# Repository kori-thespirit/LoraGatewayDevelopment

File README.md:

# ESP32-S3 Pin Mapping Documentation

Tài liệu này mô tả sơ đồ kết nối chân giữa ESP32-S3 và các module sử dụng trong hệ thống.

---

# 1. Strapping Pins (Boot Configuration)

Các chân này được đọc khi ESP32 khởi động, ảnh hưởng đến chế độ boot và cấu hình phần cứng.

| ESP32-S3 | FUNCTION |
|:---------|:---------|
| GPIO0    | Boot mode select |
| GPIO3    | JTAG source select |
| GPIO45   | Flash voltage select |
| GPIO46   | Boot mode / ROM log control |

---

# 2. LoRa Module (SPI)

Ví dụ module: SX1278 / Ra-02

| ESP32-S3 | LORA |
|:---------|:-----|
| GPIO40   | MISO |
| GPIO39   | SCK |
| GPIO41   | MOSI |
| GPIO42   | NSS (CS) |
| GPIO38   | RST |
| GPIO37   | DIO0 |

---

# 3. RS485 Module (UART)

Ví dụ module: MAX3485 / SP3485

| ESP32-S3 | RS485 |
|:---------|:------|
| GPIO17   | TX |
| GPIO18   | RX |
| GPIO16   | DE |
| GPIO15   | RE |

---

# 4. I2C Devices

Ví dụ: Sensor, LCD, EEPROM

| ESP32-S3 | I2C |
|:---------|:----|
| GPIO8    | SDA |
| GPIO9    | SCL |

---

# 5. SPI Devices (General)

| ESP32-S3 | SPI DEVICE |
|:---------|:-----------|
| GPIO12   | MISO |
| GPIO13   | MOSI |
| GPIO14   | SCK |
| GPIO10   | CS |

---

# 6. UART Debug / Programming

| ESP32-S3 | UART |
|:---------|:-----|
| GPIO43   | TXD0 |
| GPIO44   | RXD0 |

---

# 7. Control Signals

| ESP32-S3 | CONTROL |
|:---------|:--------|
| EN       | Chip enable / Reset |
| 3V3      | Power supply |
| GND      | Ground |

---

# 8. Important Notes

## Strapping Pins Warning

Không nên kéo các chân sau xuống mức LOW khi khởi động:

- GPIO0
- GPIO3
- GPIO45
- GPIO46

Sai cấu hình có thể gây:

- Không boot
- Không nạp code
- Treo hệ thống

## Recommended Pull-up / Pull-down

- GPIO0 → Pull-up 10kΩ
- EN → Pull-up 10kΩ

---

# 9. Project Information

## MCU

ESP32-S3

## Communication

- SPI
- UART
- RS485
- I2C

---

# End of Document

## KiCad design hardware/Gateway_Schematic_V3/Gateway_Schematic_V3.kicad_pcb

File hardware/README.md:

# ESP32-S3 Pin
| Pin Number | Pin Name | Function | Device |
| :--- | :--- | :--- | :--- |
| 5 | GPIO5 (ESP_TX) | HMI_RX | HMI Dwin |
| 6 | GPIO6 (ESP_RX) | HMI_TX | HMI Dwin |
| 39 | GPIO1 | LoRA_INTERRUPT | LoRA Module |
| 31 | GPIO38 | RESET | LoRA Module |
| 32 | GPIO39 | SCK | LoRA Module |
| 33 | GPIO40 | MISO | LoRA Module |
| 34 | GPIO41 | MOSI | LoRA Module |
| 35 | GPIO42 | CS | LoRA Module |
| 18 | GPIO10 | I2C_SCL | Module RTC_DS3231 |
| 19 | GPIO11 | I2C_SDA | Module RTC_DS3231 |
| 15 | GPIO3 | SIM_PWRKEY | SIMCOM |
| 7 | GPIO7 | SIM_RESET | SIMCOM |
| 23 | GPIO21 (ESP_TX) | SIM_RX | SIMCOM |
| 24 | GPIO47 (ESP_RX) | SIM_TX | SIMCOM |
| 12 | GPIO8 | CS | W5500_ETHERNET |
| 17 | GPIO9 | INTERRUPT | W5500_ETHERNET |
| 9 | GPIO16 | MOSI | W5500_ETHERNET |
| 10 | GPIO17 | MISO | W5500_ETHERNET |
| 11 | GPIO18 | SPI_CLK | W5500_ETHERNET |
| 22 | GPIO14 | SDIO_CLK | SD CARD |
| 8 | GPIO15 | SDIO_CMD | SD CARD |
| 20 | GPIO12 | SDIO_DATA0 | SD CARD |
| 21 | GPIO13 | SDIO_DATA1 | SD CARD |
| 4 | GPIO4 | SDIO_DATA2 | SD CARD |
| 38 | GPIO2 | SDIO_DATA3 | SD CARD |
| 26 | GPIO45 | SDIO_DET | SD CARD |

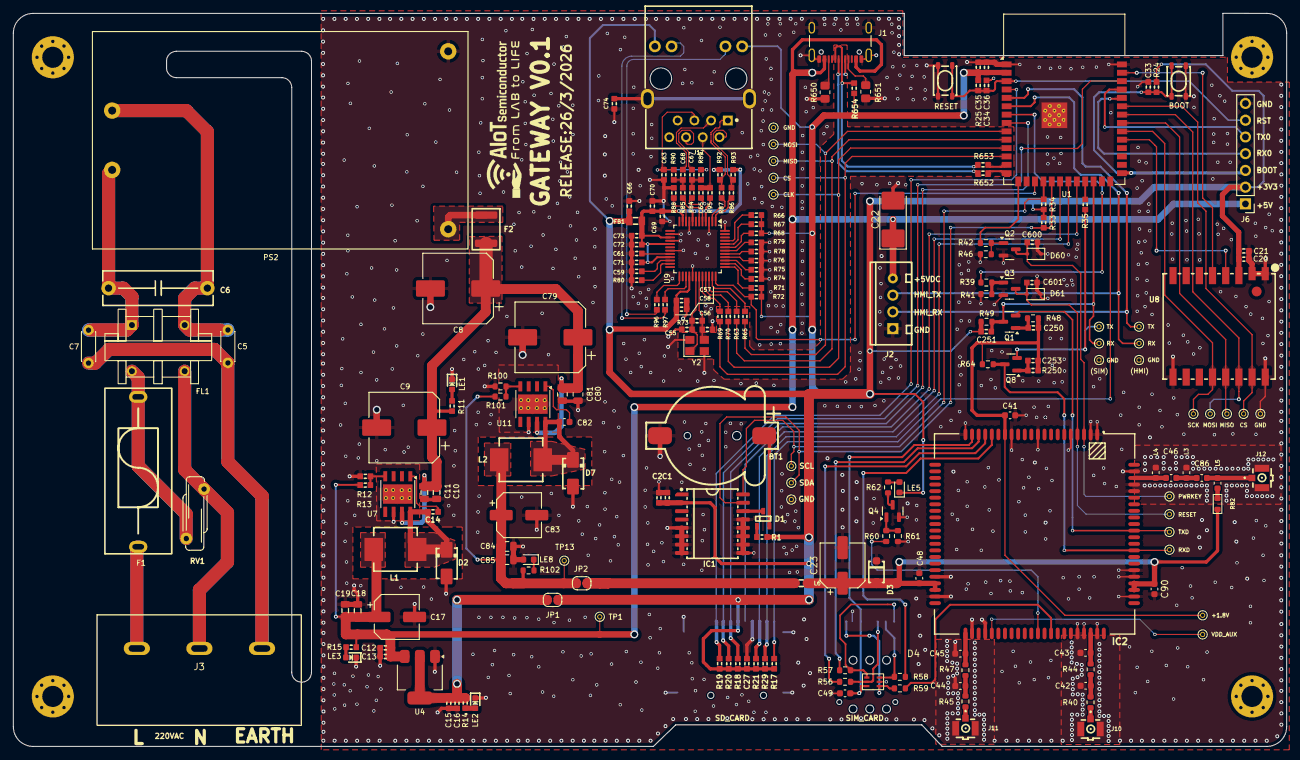
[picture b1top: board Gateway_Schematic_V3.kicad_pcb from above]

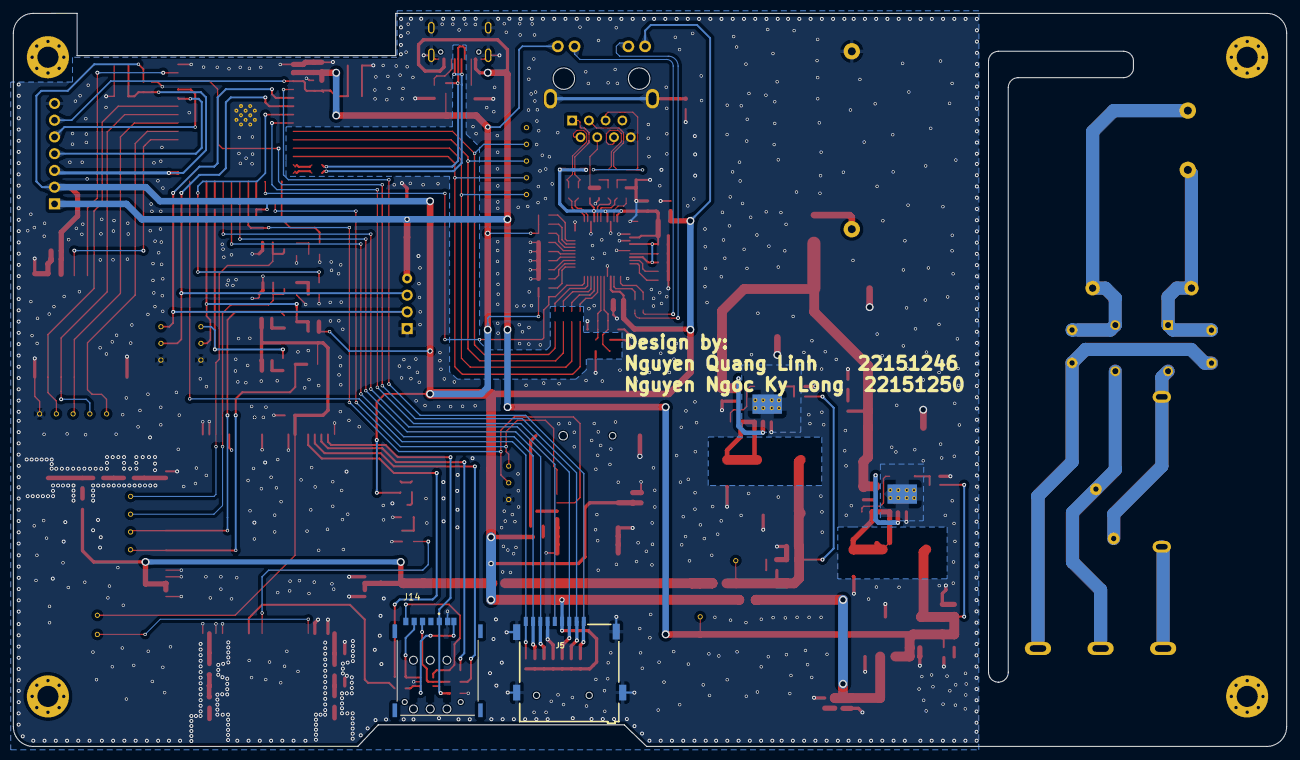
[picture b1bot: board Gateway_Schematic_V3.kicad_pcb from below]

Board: 2 copper layers, 193.2 x 111.3 mm, 222 parts (2 on the bottom side), 132 nets.

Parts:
+1.8V: TestPoint_throughtHole_D1.0mm
BT1: CR1220; BatteryHolder_CR1220
C1, C20, C36, C66: 10uF; C_0603
C2, C13, C16, C21, C27, C33, C35, C58, C69, C70, C71, C72, C73, C600, C601: 100nF; C_0603
C5, C7: 471/2k; C_Disc_D4.3mm_W1.9mm_P5.00mm
C6: 0.1uF/275VAC; C_Rect_L16.5mm_W5.0mm_P15.00mm_MKT
C8, C9, C79: 470uF/35V; CP_Elec_10x10.5
C10, C18: 10uF; C_0805
C11, C19: 100nF; C_0805
C12, C15, C34, C57: 1uF; C_0603
C14, C59, C63: 10nF; C_0603
C17, C83: 330uF/6v3; CP_Elec_6.3x7.7
C22: 100uF/35V/7343; CP_EIA-7132-28_AVX-C_Pad2.72x3.50mm_HandSolder
C23: C_Polarized; CP_Elec_6.3x7.7
C41, C49: 100nF; C_0603_1608Metric
C42, C43, C44, C45: NC; C_0603_1608Metric
C46, C48, C86: 33pF; C_0603_1608Metric
C55, C56: 18pF; C_0603
C61: 4.7uF; C_0603
C65: 22nF; C_0603
C67, C68: 6.8nF; C_0603
C74: 4.7nF; C_0603
C80, C84: 10uF; C_0805_2012Metric
C81, C85: 100nF; C_0805_2012Metric
C82: 10nF; C_0603_1608Metric
C90: 18pF; C_0603_1608Metric
C250, C253: 1nF; C_0603
C251: 470pF; C_0603
CLK: TestPoint_throughtHole_D1.0mm
CS: TestPoint; TestPoint_throughtHole_D1.0mm
CS#2: TestPoint_throughtHole_D1.0mm
D1: BAT54C; SOT23-3
D2, D7: SS54; D_SMA
D3: 5V1; D_SOD-123
D4: SMF05C; SC70-6
D60, D61: PSD12C; D_SOD-323
F1: 2A; Fuse_HolderGlass5x20mm
F2: 1.5A; Fuse_1812_4532Metric
FB1: FerriteBead_Small; L_0805
FL1: 20mH; ACFilterChokeUU9.8
GND: TestPoint; TestPoint_throughtHole_D1.0mm
GND#2, GND#3, GND#4, GND#5: TestPoint; TestPoint_throughtHole_D1.0mm
H1, H1#2, H1#3, H1#4: MountingHole; MountingHole_3.2mm_M3_Pad_Via
IC1: RTC_DS3231M; SOIC-16W_7.5x10.3mm_P1.27mm
IC2: SIM7600CE-H; SIM7600
J1: USB_C_Receptacle_USB2.0_14P; USB_C_Receptacle_GCT_USB4105-xx-A_16P_TopMnt_Horizontal
J2: Conn_01x04_Pin; Conn_XH-P2.54mm-4P
J3: Screw_Terminal_01x03; TerminalBlock_Screw_HB9500_3pin_P9.5mm
J5: MiSD-PP-9P-V1; MicroSD_Socket_9P
J6: Conn_01x07_Pin; PinHeader_1x07_P2.54mm_Vertical
J10, J11, J12: ANT_LTE; Conn_IPEX_ANT
J14: SIM7100-6pin-socket-smd; CUI_NSIM-1-A
J17: HR911105A; HANRUN_RJ45LED_HR911105A
JP1, JP2: SolderJumper_2_Open; SolderJumper-2_P1.3mm_Open_RoundedPad1.0x1.5mm
L1, L2: 15uH; L_6.6x6.6
L3, L4, L5: L; L_0603_1608Metric
L6: L_Ferrite_Small; L_0805
LE1, LE2, LE3: Led; LED_0603
LE5, LE8: Led; LED_0603_1608Metric
MISO: TestPoint; TestPoint_throughtHole_D1.0mm
MISO#2: TestPoint_throughtHole_D1.0mm
MOSI: TestPoint; TestPoint_throughtHole_D1.0mm
MOSI#2: TestPoint_throughtHole_D1.0mm
PS2: HLK-20M12; ACDC_HLK-20MXX
PWRKEY: TestPoint_throughtHole_D1.0mm
Q1, Q8: MMBT3904; SOT-23
Q2, Q3, Q4: BC817; SOT-23
R1: 1K/0603/5%; R_0603
R11, R13: 10k; R_0603
R12: 3k3; R_0603
R14, R15: 1k; R_0603
R17, R18, R19, R20, R21, R24, R25, R29, R33, R34: 10K/0603/1%; R_0603
R35: 100R; R_0603
R39, R42, R48, R49, R60, R64, R100: 4K7; R_0603_1608Metric
R40, R44, R45, R47, R59: 0; R_0603_1608Metric
R41, R46, R61: 47K; R_0603_1608Metric
R56, R57, R58: 22; R_0603_1608Metric
R62: 1K; R_0603_1608Metric
R63, R65, R69, R70, R84, R85, R86, R87: 33R; R_0603
R66, R67, R68, R71, R72, R74, R75, R76, R78, R79, R80: 10K; R_0603
R73: 1M; R_0603
R82: 10 Ohm; R_0603_1608Metric
R88: 12K4/1%; R_0603
R89, R90: 82R; R_0603
R92, R93: 49R9; R_0603
R95: 10R; R_0603
R96, R97: 330; R_0603
R101: 10k; R_0603_1608Metric
R102: 1k; R_0603_1608Metric
R250: 4K7; R_0603
R650, R651: 5K1; R_0805_2012Metric_Pad1.20x1.40mm_HandSolder
R652, R653: 22R; R_0603
R654: 1K5; R_0603
RESET: TestPoint_throughtHole_D1.0mm
RV1: 10D561; RV_Disc_D12mm_W5.8mm_P7.5mm
RX: TestPoint_throughtHole_D1.0mm
RX#2: TestPoint; TestPoint_throughtHole_D1.0mm
RXD: TestPoint_throughtHole_D1.0mm
SCK: TestPoint; TestPoint_throughtHole_D1.0mm
SCL: TestPoint; TestPoint_throughtHole_D1.0mm
SDA: TestPoint; TestPoint_throughtHole_D1.0mm
SW1, SW2: SW_Push; SW_SPST_PTS810
TP1: 5V; TestPoint_throughtHole_D1.0mm
TP13: 4V; TestPoint_throughtHole_D1.0mm
TX: TestPoint_throughtHole_D1.0mm
TX#2: TestPoint; TestPoint_throughtHole_D1.0mm
TXD: TestPoint_throughtHole_D1.0mm
U1: ESP32-S3-WROOM-1
U4: AMS1117-3.3; SOT-223-3_TabPin2
U7, U11: TPS5430DDA; TI_SO-PowerPAD-8_ThermalVias
U8: SX1278 Lora Ra-02; MODULE_RA-02_LORA
U9: W5500; LQFP-48_7x7mm_P0.5mm
VDD_AUX: TestPoint_throughtHole_D1.0mm
Y2: 25MHz; Crystal_SMD_3225-4Pin_3.2x2.5mm

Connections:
+3.3V: C1.2, C2.2, C15.2, C16.2, C20.1, C21.1, C27.2, C35.1, C36.1, C57.1, C58.1, C66.1, C251.1, FB1.2, IC1.2 (VCC), J5.4 (VDD), J6.2, J17.9, J17.12, JP1.1 (A), JP1.2 (B), LE5.1, R1.1, R14.1, R17.1, R18.1, R19.1, R20.1, R21.1, R24.1, R25.1, R29.1, R33.1, R34.1, R49.2, R66.1, R67.1, R68.1, R71.1, R72.1, R654.2, U1.2 (3V3), U4.2 (VO), U8.3 (VDD), U9.28 (VDD)
+4V: C23.1, C48.1, C83.1, C84.1, C85.1, C90.1, D3.1 (K), IC2.38 (VBAT), IC2.39 (VBAT), IC2.62 (VBAT), IC2.63 (VBAT), JP2.1 (A), JP2.2 (B), L2.2, L6.1, L6.2, R82.1, R101.2, R102.1, TP13.1
+5V: C12.2, C13.2, C17.1, C18.1, C19.1, C22.1, J1.A4 (VBUS), J1.A9 (VBUS), J1.B4 (VBUS), J1.B9 (VBUS), J2.4, J6.1, L1.2, R13.2, R15.1, TP1.1, U4.3 (VI)
+12V: C8.1, C9.1, C10.1, C11.1, C79.1, C80.1, C81.1, F2.2, R11.1, U7.7 (VIN), U11.7 (VIN)
/ESP32-S3/BOOT: C33.1, J6.3, R24.2, SW1.2, U1.27 (IO0)
/ESP32-S3/ESP.CLK: J5.5 (CLK), U1.22 (IO14)
/ESP32-S3/ESP.CMD: J5.3 (CMD), R18.2, U1.8 (IO15)
/ESP32-S3/ESP.DATA0: J5.7 (DAT0), R21.2, U1.20 (IO12)
/ESP32-S3/ESP.DATA1: J5.8 (DAT1), R29.2, U1.21 (IO13)
/ESP32-S3/ESP.DATA2: J5.1 (DAT2), R19.2, U1.4 (IO4)
/ESP32-S3/ESP.DATA3: J5.2 (DAT3/CD), R20.2, U1.38 (IO2)
/ESP32-S3/ESP.DET: J5.9 (DET), R17.2, U1.26 (IO45)
/ESP32-S3/ESP.SCL: IC1.16 (SCL), R34.2, SCL.1, U1.18 (IO10)
/ESP32-S3/ESP.SDA: IC1.15 (SDA), R33.2, SDA.1, U1.19 (IO11)
/ESP32-S3/ESP.USB_N: R653.2, U1.13 (IO19)
/ESP32-S3/ESP.USB_P: R652.2, U1.14 (IO20)
/ESP32-S3/ESP_ETH.CLK: CLK.1, R70.1, U1.11 (IO18)
/ESP32-S3/ESP_ETH.MISO: MISO#2.1, R63.1, U1.10 (IO17)
/ESP32-S3/ESP_ETH.MOSI: MOSI#2.1, R65.1, U1.9 (IO16)
/ESP32-S3/ESP_ETH_CS: CS#2.1, R69.1, U1.12 (IO8)
/ESP32-S3/ESP_ETH_INT: R72.2, U1.17 (IO9), U9.36 (~INT)
/ESP32-S3/ESP_HMI_RX: J2.3, RX#2.1, U1.6 (IO6)
/ESP32-S3/ESP_HMI_TX: J2.2, TX#2.1, U1.5 (IO5)
/ESP32-S3/LORA.CS: CS.1, U1.35 (IO42), U8.15 (~NSS)
/ESP32-S3/LORA.INT: U1.39 (IO1), U8.5 (DIO0)
/ESP32-S3/LORA.MISO: MISO.1, U1.33 (IO40), U8.13 (MISO)
/ESP32-S3/LORA.MOSI: MOSI.1, U1.34 (IO41), U8.14 (MOSI)
/ESP32-S3/LORA.RST: U1.31 (IO38), U8.4 (~RESET)
/ESP32-S3/LORA.SCK: SCK.1, U1.32 (IO39), U8.12 (SCK)
/ESP32-S3/RST: C34.1, J6.6, R25.2, SW2.2, U1.3 (EN)
/ESP32-S3/RX0: J6.4, U1.36 (RXD0)
/ESP32-S3/TX0: J6.5, U1.37 (TXD0)
/ESP32-S3/UART1_RX: C251.2, Q1.3 (C), R49.1, RX.1, U1.24 (IO47)
/ESP32-S3/UART1_TX: Q8.2 (E), R35.2, TX.1
/Ethernet/ETH_RST: R71.2, U9.37 (~RST)
/Ethernet/ETH_VDDA: C69.1, C70.1, C71.1, C72.1, C73.1, FB1.1, R92.1, R93.1, R95.1, U9.4 (AVDD), U9.8 (AVDD), U9.11 (AVDD), U9.15 (AVDD), U9.17 (AVDD), U9.21 (AVDD)
/Khối nguồn/FB: R12.1, R13.1, U7.4 (VSENSE)
/Khối nguồn/FB4: R100.1, R101.1, U11.4 (VSENSE)
/Khối nguồn/L: F1.1, J3.1
/Khối nguồn/N: FL1.2, J3.2, RV1.1
/Khối nguồn/PH: C14.2, D2.2, L1.1, U7.8 (PH)
/Khối nguồn/PH4: C82.2, D7.2, L2.1, U11.8 (PH)
/Khối nguồn/fuse: F2.1, PS2.4 (+Vout)
/SIMCOM/ESP_PWRKEY: R42.1, U1.15 (IO3)
/SIMCOM/ESP_RST: R39.1, U1.7 (IO7)
/SIMCOM/PWRKEY: C600.1, D60.2 (A2), IC2.3 (PWRKEY), PWRKEY.1, Q2.3 (C)
/SIMCOM/RESET: C601.1, D61.2 (A2), IC2.4 (RESET), Q3.3 (C), RESET.1
/SIMCOM/RXD: IC2.68 (RXD), Q8.3 (C), R64.1, RXD.1
/SIMCOM/TXD: IC2.71 (TXD), Q1.2 (E), TXD.1
/SIMCOM/VDD_1_8V: +1.8V.1, C41.1, C250.1, C253.2, IC2.15 (VDD_EXT), R48.2, R64.2, R250.2
Earth: C5.2, C7.1, J3.3
GND: BT1.2 (-), C1.1, C2.1, C8.2, C9.2, C10.2, C11.2, C12.1, C13.1, C15.1, C16.1, C17.2, C18.2, C19.2, C20.2, C21.2, C22.2, C23.2, C27.1, C33.2, C34.2, C35.2, C36.2, C41.2, C42.1, C43.1, C44.1, C45.1, C48.2, C49.2, C55.1, C56.1, C57.2, C58.2, C59.1, C61.1, C63.1, C65.1, C66.2, C69.2, C70.2, C71.2, C72.2, C73.2, C74.2, C79.2, C80.2, C81.2, C83.2, C84.2, C85.2, C90.2, C600.2, C601.2, D2.1, D3.2 (A), D4.2, D7.1, D60.1 (A1), D61.1 (A1), GND#2.1, GND#3.1, GND#4.1, GND#5.1, IC1.5 (GND), IC1.6 (GND), IC1.7 (GND), IC1.8 (GND), IC1.9 (GND), IC1.10 (GND), IC1.11 (GND), IC1.12 (GND), IC1.13 (GND), IC2.1 (GND), IC2.2 (GND), IC2.5 (GND), IC2.10 (GND), IC2.14 (GND), IC2.37 (GND), IC2.40 (GND), IC2.41 (GND), IC2.43 (GND), IC2.57 (GND), IC2.58 (GND), IC2.60 (GND), IC2.61 (GND), IC2.64 (GND), IC2.65 (GND), IC2.77 (GND), IC2.78 (GND), IC2.80 (GND), IC2.81 (GND), J1.A1 (GND), J1.A12 (GND), J1.B1 (GND), J1.B12 (GND), J1.S1 (SHIELD), J2.1, J5.6 (VSS), J5.10 (SHIELD), J6.7, J10.2 (Ext), J11.2 (Ext), J12.2 (Ext), J14.C5 (GND), J17.8, L3.2, L4.2, LE1.2, LE2.2, LE3.2, LE8.2, PS2.3 (-Vout), Q2.2 (E), Q3.2 (E), Q4.2 (E), R12.2, R41.2, R46.2, R61.2, R74.1, R75.1, R76.1, R78.1, R79.1, R80.1, R88.2, R100.2, R650.2, R651.2, SW1.1, SW2.1, U1.1 (GND), U1.40 (GND), U1.41 (GND), U4.1 (GND), U7.6 (GND), U7.9 (GNDPAD), U8.1 (GND), U8.2 (GND), U8.9 (GND), U8.16 (GND), U9.3 (AGND), U9.9 (AGND), U9.14 (AGND), U9.16 (AGND), U9.19 (AGND), U9.29 (GND), U9.48 (AGND), U11.6 (GND), U11.9 (GNDPAD), Y2.2, Y2.4
unnamed: BT1.1 (+), D1.2
unnamed: C42.2, R40.2, R44.1
unnamed: C44.2, R45.2, R47.1
unnamed: C46.2, C86.1, L3.1
unnamed: C63.2, J17.5, R89.2, R90.2
unnamed: C65.2, J17.4, R95.2
unnamed: C67.1, R84.2, R89.1
unnamed: C67.2, J17.6
unnamed: C68.1, R85.2, R90.1
unnamed: C68.2, J17.3
unnamed: D1.1, R1.2
unnamed: D4.1, J14.CD, R59.2
unnamed: F1.2, FL1.4, RV1.2
unnamed: D1.3, IC1.14 (VBAT)
unnamed: C43.2, IC2.59 (AUX_ANT), R44.2
unnamed: C46.1, IC2.79 (GNSS_ANT), L4.1
unnamed: C45.2, IC2.82 (MAIN_ANT), R47.2
unnamed: IC2.51 (NETLIGHT), R60.1
unnamed: IC2.19 (USIM_CLK), R57.1
unnamed: IC2.17 (USIM_DATA), R58.1
unnamed: IC2.53 (USIM_DET), R59.1
unnamed: IC2.18 (USIM_RST), R56.1
unnamed: C49.1, D4.6, IC2.20 (USIM_VDD), J14.C1 (VCC)
unnamed: IC2.44 (VDD_AUX), VDD_AUX.1
unnamed: J1.A5 (CC1), R651.1
unnamed: J1.B5 (CC2), R650.1
unnamed: J1.A6 (D+), J1.B6 (D+), R653.1, R654.1
unnamed: J1.A7 (D-), J1.B7 (D-), R652.1
unnamed: J10.1 (In), R40.1
unnamed: J11.1 (In), R45.1
unnamed: C86.2, J12.1 (In), L5.2
unnamed: D4.4, J14.C3 (CLK), R57.2
unnamed: D4.3, J14.C7 (I/O), R58.2
unnamed: D4.5, J14.C2 (RST), R56.2
unnamed: J17.1, R87.2, R92.2
unnamed: J17.2, R86.2, R93.2
unnamed: J17.10, R96.2
unnamed: J17.11, R97.2
unnamed: C74.1, J17.SH (SHIELD)
unnamed: L5.1, R82.2
unnamed: LE1.1, R11.2
unnamed: LE2.1, R14.2
unnamed: LE3.1, R15.2
unnamed: LE5.2, R62.2
unnamed: LE8.1, R102.2
unnamed: C5.1, C6.1, FL1.3, PS2.1 (AC/L)
unnamed: C6.2, C7.2, FL1.1, PS2.2 (AC/N)
unnamed: C250.2, Q1.1 (B), R48.1
unnamed: Q2.1 (B), R42.2, R46.1
unnamed: Q3.1 (B), R39.2, R41.1
unnamed: Q4.1 (B), R60.2, R61.1
unnamed: Q4.3 (C), R62.1
unnamed: C253.1, Q8.1 (B), R250.1
unnamed: R74.2, U9.38 (RSVD)
unnamed: R75.2, U9.39 (RSVD)
unnamed: R76.2, U9.40 (RSVD)
unnamed: R78.2, U9.41 (RSVD)
unnamed: R79.2, U9.42 (RSVD)
unnamed: R80.2, U9.23 (RSVD)
unnamed: R35.1, U1.23 (IO21)
unnamed: C14.1, U7.1 (BOOT)
unnamed: C59.2, U9.22 (1V2O)
unnamed: R97.1, U9.27 (ACTLED)
unnamed: R88.1, U9.10 (EXRES1)
unnamed: R96.1, U9.25 (LINKLED)
unnamed: R63.2, U9.34 (MISO)
unnamed: R65.2, U9.35 (MOSI)
unnamed: R66.2, U9.45 (PMODE0)
unnamed: R67.2, U9.44 (PMODE1)
unnamed: R68.2, U9.43 (PMODE2)
unnamed: R84.1, U9.5 (RXN)
unnamed: R85.1, U9.6 (RXP)
unnamed: R70.2, U9.33 (SCLK)
unnamed: C61.2, U9.20 (TOCAP)
unnamed: R86.1, U9.1 (TXN)
unnamed: R87.1, U9.2 (TXP)
unnamed: C55.2, R73.1, U9.30 (XI/CLKIN), Y2.1
unnamed: C56.2, R73.2, U9.31 (XO), Y2.3
unnamed: R69.2, U9.32 (~SCS)
unnamed: C82.1, U11.1 (BOOT)

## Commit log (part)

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2026-04-10 Change configuration section from Transceiver to Receiver
    Updated configuration section to reflect changes from transceiver to receiver and added relevant images.
2026-04-11 Update Receiver configuration and add flashing instructions
    Removed several images from the Receiver configuration section and added a new section for flashing the ESP32.
2026-04-12 Revise README for Wi-Fi Unit Test Module setup
    Updated the README to provide instructions in Vietnamese for setting up the Wi-Fi Unit Test Module, including cloning the project, switching branches, and configuring settings.
2026-04-12 Update path
2026-04-13 refactor: move source code to unit-test_gd20_kylong
2026-04-16 feat(modbus): update communication functions and inverter data processing - Cập nhật hàm modbud_read_single_register để hỗ trợ đọc thanh ghi đơn. - Thêm/cập nhật modbud_write_register phục vụ việc gh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
2026-04-18 Update Readme for Gateway
2026-04-19 reuploading
2026-04-20 SCRUM-61 fetch: create crc table
2026-04-20 Scrum 41 unit test lora node gd20 inverter esp32 s3 (#2)
    * Initial commit
    * Add LoRa library submodule
    * Fetch: New library ESP-MODBUS as submodule
    * SCRUM-41 Create pseudo project structure
    * SCRUM-41 Lora node tests GD20 Inverter
    * SCRUM-41 Lora node tests GD20 Inverter
2026-04-20 Scrum 28 write ethernet w5500 unit test (#5)
    * SCRUM-28 Add pseudo code
    * feat: output SPI pins success, use logic analyzer to capture
    * Fix: remove magic number
    * test: Burst transfer over 1500 byte to MOSI
    * feat: Initialize W5500 with ethernet_init dependency successfully
    * feat: Missing esp_netif_init() to get IP
2026-04-20 Revert "Scrum 41 unit test lora node gd20 inverter esp32 s3 (#2)"
    This reverts commit a9d97505672ca3303cd26e736293ab6fb5a421fa.
2026-04-20 add STM32 code
2026-04-20 reupload
2026-04-20 delte ..
2026-04-22 feat(lora) : Sent data to lora gateway
2026-04-22 feat(sensor): implement SHT20 data acquisition via RS485
2026-04-23 refactor: move unit-test project to unit-test folder
2026-04-24 Change ESP-IDF activation script path
    Updated script paths for loading ESP-IDF to new location.
2026-04-24 change source to dot
2026-04-26 refactor: create tools folder with stm32 stub and esp32
2026-04-26 experiment network components
2026-04-27 SCRUM-59 feat(mqtt): Successfully connected to broker without TLS/SSL
2026-04-27 SCRUM-59 refactor: remove wifi and ethernet folder
2026-04-27 Scrum 59 connect esp32 to vps mqtt broker with tls ssl (#15)
    * SCRUM-59 feat(wifi): Successfully get IP address
    * SCRUM-59 feat(kconfig): Use Kconfig for SSID and password
    * experiment network components
    * SCRUM-59 refactor(components): network component includes wifi_app and mqtts"
    Restructure components
    network component contains wifi_app and mqtts subcomponents
2026-04-27 feat(ignore): ignore manage_components and certificate path of MQTTS
2026-04-27 SCRUM-43 ci(workflow): build flash monitor in single script
2026-04-27 Modify build command in node.js.yml
    Updated build command to remove 'monitor' option.
2026-04-28 SCRUM-43 fix(esp32s3): update esp32s3 build path and change folder to esp32s3, fix device test in test_v2
2026-04-28 SCRUM-43 ci(name): update name CI and pytest
2026-04-28 update code for test module rtc ds3231
2026-04-28 Upload unit_test_rtc_ds3231
2026-04-28 refactor (lora gateway): test receiver from lora node
2026-04-28 refactor (lora node): test sent to lora gateway
2026-04-28 SCRUM-86 ci(pyscript): Update log capture regex
2026-04-28 SCRUM-86 fix(components): missing CMakeLists and source file
2026-04-28 SCRUM-86 ci(debug): fix log_capturer path and debug requirements
2026-04-28 SCRUM-86 fix(missing): add missing file gd20_inverter.h
2026-04-28 refactor SHT20 RS485
2026-04-28 SCRUM-86 ci(delay): adjust delay for better capture log
2026-04-28 Restore hardware folder
2026-04-29 Merge Scrum 86 cicd for gd20 modbus on gateway board (#18)
    * feat(pincfg,gateway): Use Gateway HMI UART pin to control inverter GD20
    * fix(name): rename unit test gd20 inverter for lora node and gateway
    * SCRUM-86 feat(cicd): Prepare workflow and python script
    * SCRUM-86 ci(pyscript): Update log capture regex
    * SCRUM-86 fix(name): fix workflows
    * SCRUM-86 fix(components): missing CMakeLists and source file
2026-04-29 SCRUM-87 ci(workflows): Create workflows for specific type
2026-04-29 SCRUM-87 fix experiment_debug_workflow.yml
2026-04-29 Test
2026-04-29 Simple test inputs
2026-04-29 Scrum 87 design GitHub workflow (#19)
    * SCRUM-87 ci(workflows): Create workflows for specific type
    * SCRUM-87 fix: Syntax in coordinator_workflow.yml
    * SCRUM-87 fix experiment_debug_workflow.yml
    * SCRUM-87 fix syntax main workflow
    * SCRUM-87 fix choice type in unit_test_workflow
    * Update unit_test_workflow.yml
2026-04-30 Fix indentation and formatting in workflow file
2026-04-30 Remove on.push in coordinator
2026-04-30 SCRUM-87 ci(rename): Rename unit test project option
2026-04-30 Replace ls command to tree
2026-04-30 Test evironment
2026-04-30 SCRUM-87 ci, feat(unit-test): dispatch unit test workflow with github env vars
2026-04-30 Rename unit-test_ethernet_w5500
2026-04-30 SCRUM-87 fix(pinconfig): fix SPI Ethernet pin config and add delay after initializing W5500
2026-04-30 Increase test ci delay w5500
2026-04-30 docs(Readme.md)
2026-04-30 Merge request Scrum 87 design GitHub workflow Upgrade workflow (#21)
    * SCRUM-87 ci(workflows): Create workflows for specific type
    * SCRUM-87 fix: Syntax in coordinator_workflow.yml
    * SCRUM-87 fix experiment_debug_workflow.yml
    * SCRUM-87 fix syntax main workflow
    * SCRUM-87 fix choice type in unit_test_workflow
    * Update unit_test_workflow.yml
2026-05-01 docs: change Readme.md
2026-05-01 Unit test wifi module (#13)
    * SCRUM-37 feat(wifi): implement connection to specific SSID
    * SCRUM-37 refactor: unit test wifi module
    * Build CMakeLists.txt, docs Readme.md
    * feat: SCRUM-89 move wifi_module to unit-test subfolder
    ---------
2026-05-01 chore: fix finding
2026-05-01 Correct name unit-test_wifi_module
2026-05-01 ci(env): Replace with vars.HOST_RUNNER_PATH in unit_test_workflow
2026-05-01 ci(coordinator): change unit test to mqtts_vps_broker to reduce test overhead
2026-05-01 ci(log): Add LOG START and LOG END to capture log
2026-05-01 re upload
2026-05-01 chora: change path
2026-05-01 fix(wifi,build): change source file name
2026-05-01 SCRUM-56 fix(unit-test): discard unit-test_modbus_gd20_inverter
2026-05-01 Scrum 56 improve baremetal modbus library trial uart interrupt (#20)
    * Initial commit
    * Add LoRa library submodule
    * Fetch: New library ESP-MODBUS as submodule
    * SCRUM-41 Create pseudo project structure
    * SCRUM-41 Lora node tests GD20 Inverter
    * SCRUM-41 Lora node tests GD20 Inverter
2026-05-03 fix(path): remove code/code/unit-test path
2026-05-03 Refactor SD card handling in main.c
    Refactor SD card initialization and file handling with improved comments and structure.
2026-05-05 SCRUM-91 change: Update comments for clarity in main.c
2026-05-06 SCRUM-92 feat(SIM7600): test sent AT command
2026-05-08 feat(cert): Reuse unit-test_mqtts_vps_broker, add kolabori.pem certificate, test TLS/SSL successfully
2026-05-08 SCRUM-103 fix(cert): add certificates folder to git cache
2026-05-09 MR: Unit test MQTTS User Authenticate (#25)
    * feat(cert): Reuse unit-test_mqtts_vps_broker, add kolabori.pem certificate, test TLS/SSL successfully
    * SCRUM-103 ci(unit-test): add unit-test_mqtts_user_authenticate to github workflow
    * SCRUM-103 fix(cert): add certificates folder to git cache
    * feat(kconfig): add MQTT username and password to Kconfig, authenticate successfully
    ---------
2026-05-09 SCRUM-97 feat(core): Create core folder contains gateway and node Lora
2026-05-09 SCRUM-97 refactor(lora,define): change Lora SPI name in lora.c library
2026-05-09 SCRUM-97 feat(gateway,task): build static Lora and network pin core 1 pass, not test yet
2026-05-09 SCRUM-97 feat(common): add common task and increase stack size lora task
2026-05-11 SCRUM-97 Add LICENSE placeholder and add enum task priority
2026-05-11 SCRUM-100 build(lora_protocol): add lora_protocol in middleware folder and build successfully
2026-05-13 SCRUM-100 feat: add MIN macro define
2026-05-13 SCRUM-100 fix(callback): fix callback lora_protocol and test SHT20 packet
2026-05-14 SCRUM-100 fix(callback): revert return value to void for lorar_protocol callback function
2026-05-14 SCRUM-100 fix(protocol): successfully send SHT20 data
2026-05-16 SCRUM-97 fix(esp_log): remove ESP log in lora_protocol, add new error code and update error check flow code
2026-05-18 write draft
2026-05-19 SCRUM 90: Update Unit code for DWIN
2026-05-19 SCRUM-90 feat(hmi): Porting HMI Arduino code to ESP-IDF, build success, not test
2026-05-23 SCRUM_90:Update ESP_IDF code (Text Keyboard for Wifi)
2026-05-27 feat: add modbus driver callback handler and move node_device_typedef to modbus middleware
2026-05-29 feat(enum modbus function): shorten enum MODBUS_ to MB_
2026-05-30 Add note lora protocol
2026-05-30 SCRUM-113 feat(CMake): Add modbus_payload_handle source path and require for main CMakeLists
2026-05-31 SCRUM-113 refactor(callback): move callback features from modbus_application_driver components to middleware modbus payload handle
2026-05-31 SCRUM-113 style(argument): simplify modbus_send argument name
2026-05-31 SCRUM-113 refactor: remove modbud_write_register_with_fb
2026-06-01 SCRUM-113 feat(m_modbus_payload_handle): Reset static variable
2026-06-01 SCRUM-115 feat(main): Add network task handle and enum task id
2026-06-01 upload code
2026-06-03 SCRUM-113 fix rx_callback of modbus middleware
2026-06-03 SCRUM-115 fix: remove payload_typedef.h
2026-06-05 SCRUM-115 feat(datacore): add data core typedef, change middleware modbus member to reg in modbus descriptor
2026-06-07 Scrum 90 design and communication between dwin and esp32 (#27)
    * SCRUM-90 feat(DWIN): unit test communication between ESP32S3 and DWIN display using Arduino IDE
    * SCRUM_90:FEAT(Design_UI)
    * SCRUM 90: Update Unit code for DWIN
    * SCRUM-90 feat(hmi): rename unit-test_hmi_dwin and build successfully
    * SCRUM-90 feat(hmi): Porting HMI Arduino code to ESP-IDF, build success, not test
    * SCRUM_90:Update ESP_IDF code DWIN - ESP32
2026-06-09 SCRUM-115 feat(gw mb driver): update modbus driver from node
2026-06-09 SCRUM-115 feat(misc): Update data_typedef, middleware modbus and intertask
    data_typedef: Add lora_data and lora_config_reg
    middleware modbus: Add handle MB_FUNC_R_INPUT
    intertask: add is_request member
2026-06-09 SCRUM-115 feat(node): Add intertask logic code
    - Update lora_task logic to support new update lora_protocol middleware
    - Handle new error code of modbus middleware MB_PAYLOAD_ERR_MODBUS_TYPE to check supported modbus function
2026-06-09 SCRUM-115 feat(hmi): Add HMI DGUS registry
2026-06-10 SCRUM-102 feat(hmi driver): update hmi_event_cb
2026-06-12 SCRUM-115 style(lora_protocol): styling M_LORA_ASSERT_DEFINE
2026-06-13 SCRUM-102 feat(hmi): update HMI driver logic code
    Add HMI parse callback handle
    Add struct st_hmi_frame_t
2026-06-14 SCRUM-115,SCRUM-102 feat: Successfully control GD20 inverter via HMI DWIN
    Fix logic of lora_protocol
    Reduce core data size to 20
    Reduce lora buffer size
    Add raw logic of send text to HMI
2026-06-16 SCRUM-115 perf(node): remove vTaskDelay 3000 in task loop
2026-06-16 SCRUM-115 feat(SHT20 node): memcpy to SHT20 core data id
2026-06-17 SCRUM-105 feat(modbus): support GD20_CONVERTER_TEMP
2026-06-17 SCRUM-115 feat(gd20 converter temp): support GD20 params in gateway
2026-06-18 SCRUM_115: update hmi_task and set_frequency_to_inverter
2026-06-28 SCRUM-115 feat(queue): Create each q_common for each task handle id
2026-06-28 SCRUM-115 feat(common): common task handle request modbus data
2026-06-28 SCRUM-101 feat(gw): successfully connected to MQTT broker
2026-06-28 SCRUM-101 feat(mqtt): Successfully sub and pub to broker
2026-06-28 SCRUM-101 feat(code size): Increase flash size partition table
2026-06-28 SCRUM-101 draft(topic): Add handle_topic_request
2026-06-28 SCRUM-101 feat: Create topic handle data structure
